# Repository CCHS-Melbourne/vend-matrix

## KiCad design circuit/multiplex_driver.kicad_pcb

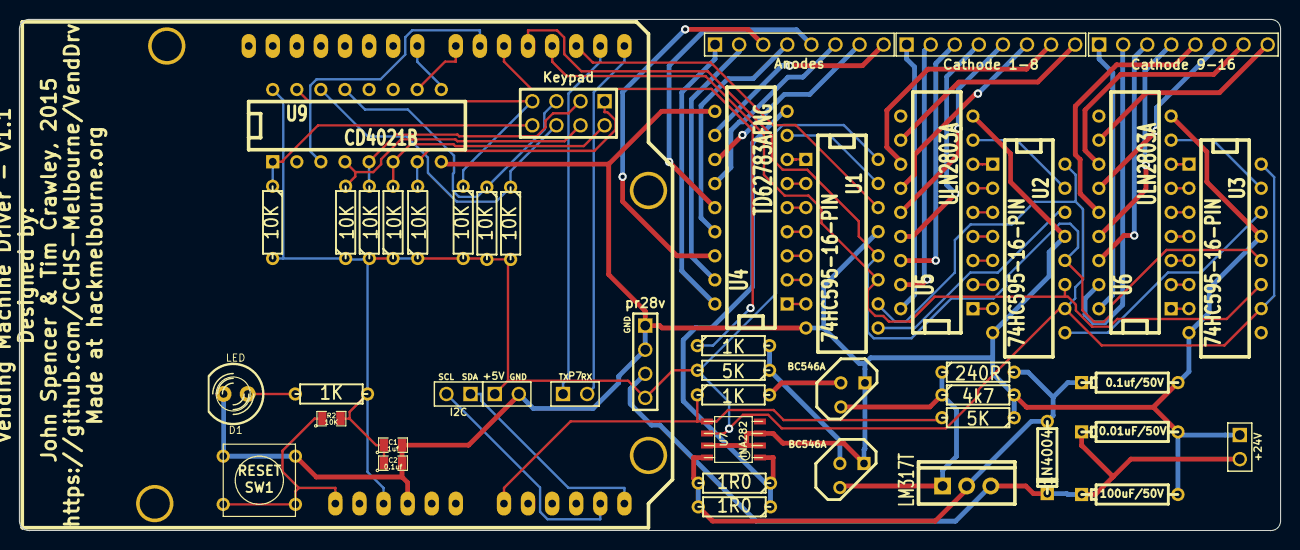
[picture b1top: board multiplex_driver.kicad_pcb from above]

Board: 2 copper layers, 133.0 x 53.9 mm, 47 parts (0 on the bottom side), 80 nets.

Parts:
C1: 1uf; SM0805
C2: 0.1uf; SM0805
C3: 100uF/50V; CP4
C4: 0.01uF/50V; CP4
C5: 0.1uf/50V; CP4
D1: LED; LED-5MM
D2: 1N4004; D3
P1: Keypad; pin_array_4x2
P2: I2C; PIN_ARRAY_2X1
P3: +5V; PIN_ARRAY_2X1
P4: Anodes; pin_array_8x1
P5: Cathode 1-8; pin_array_8x1
P6: Cathode 9-16; pin_array_8x1
P7: Serial; PIN_ARRAY_2X1
P8: +24V; PIN_ARRAY_2X1
P9: pr28v; PIN_ARRAY_4x1
Q1, Q2: BC546A; TO92
R1, R3, R6: 1K; R3
R2: 10K; SM0805
R4, R8: 5K; R3
R5: 4k7; R3
R7: 240R; R3
R9, R10: 1R0; R3
R11, R12, R13, R14, R15, R16, R17, R18: 10K; R3
SHIELD1: ARDUINO_SHIELD
SW1: RESET; SW_PUSH_SMALL
U1, U2, U3: 74HC595-16-PIN; DIP-16__300
U4: TD62783AFNG; DIP-18__300
U5, U6: ULN2803A; DIP-18__300
U7: INA282; so-8
U8: LM317T
U9: CD4021B; DIP-16__300

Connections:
+5V: C1.1, C2.1, P3.1, P9.4, R1.1, R2.2, R8.2, R11.1, R12.1, R13.1, R14.2, R15.2, R16.2, R17.2, R18.1, SHIELD1.5V, U1.10, U1.16, U2.10, U2.16, U3.10, U3.16, U7.6, U9.16
+24V: C3.1, C4.1, D2.2, P8.2, P9.3, U8.3
GND: C1.2, C2.2, C3.2, C4.2, C5.2, D1.2, P3.2, P8.1, P9.1, P9.2, Q1.1, Q2.1, R4.1, R5.2, SHIELD1.GND1, SW1.2, U1.8, U1.13, U2.8, U2.13, U3.8, U3.13, U4.10, U5.9, U6.9, U7.2, U7.3, U7.7, U9.8
K-RCLK: SHIELD1.8, U9.9
K-SER: SHIELD1.6, U9.3
K-SRCLK: SHIELD1.7, U9.10
M-ON/OFF: R3.1, SHIELD1.5
M-RCLK: SHIELD1.4, U1.12, U2.12, U3.12
M-SENSE: R4.2, R6.1, SHIELD1.AD0, U7.5
M-SER: SHIELD1.2, U1.14
M-SRCLK: SHIELD1.3, U1.11, U2.11, U3.11
MOTOR+: R9.1, R10.1, U4.9, U7.1
unnamed: U3.2, U6.6
unnamed: U3.7, U6.1
unnamed: U3.6, U6.2
unnamed: U3.5, U6.3
unnamed: U3.4, U6.4
unnamed: U3.3, U6.5
unnamed: U2.5, U5.3
unnamed: U2.4, U5.4
unnamed: U2.3, U5.5
unnamed: U3.15, U6.8
unnamed: U3.1, U6.7
unnamed: P2.1, SHIELD1.AD5
unnamed: P2.2, SHIELD1.AD4
unnamed: P5.7, U5.12
unnamed: P5.8, U5.11
unnamed: P6.1, U6.18
unnamed: P6.2, U6.17
unnamed: P6.3, U6.16
unnamed: P6.4, U6.15
unnamed: P6.5, U6.14
unnamed: P6.6, U6.13
unnamed: P6.7, U6.12
unnamed: P6.8, U6.11
unnamed: P5.6, U5.13
unnamed: U1.15, U4.8
unnamed: U1.1, U4.7
unnamed: U1.2, U4.6
unnamed: P4.4, U4.15
unnamed: P4.1, U4.18
unnamed: P4.2, U4.17
unnamed: P4.3, U4.16
unnamed: P4.5, U4.14
unnamed: P4.6, U4.13
unnamed: P4.7, U4.12
unnamed: P4.8, U4.11
unnamed: P5.1, U5.18
unnamed: P5.2, U5.17
unnamed: P5.3, U5.16
unnamed: P5.4, U5.15
unnamed: P5.5, U5.14
unnamed: U2.15, U5.8
unnamed: U2.1, U5.7
unnamed: U2.2, U5.6
unnamed: U2.7, U5.1
unnamed: U2.6, U5.2
unnamed: U1.5, U4.3
unnamed: U1.7, U4.1
unnamed: U1.6, U4.2
unnamed: U1.4, U4.4
unnamed: U1.3, U4.5
unnamed: P1.1, R11.2, U9.7
unnamed: P7.1, SHIELD1.1
unnamed: P7.2, SHIELD1.0
unnamed: P1.8, R14.1, U9.1
unnamed: P1.7, R15.1, U9.15
unnamed: P1.5, R17.1, U9.13
unnamed: P1.4, R18.2, U9.4
unnamed: P1.3, R13.2, U9.5
unnamed: P1.2, R12.2, U9.6
unnamed: P1.6, R16.1, U9.14
unnamed: D1.1, R1.2
unnamed: Q2.2, R6.2
unnamed: U2.9, U3.14
unnamed: R2.1, SHIELD1.RST, SW1.1
unnamed: U1.9, U2.14
unnamed: Q1.2, R3.2, R8.1
unnamed: C5.1, D2.1, R7.2, R9.2, R10.2, U7.8, U8.2
unnamed: Q1.3, Q2.3, R5.1, R7.1, U8.1

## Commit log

2015-01-23 :circus_tent: Added .gitattributes & .gitignore files
2015-01-23 first version
    Bit of a mix of full arduino and attiny
2015-01-24 Added input for keypad
    the uno model includes the ability to connect to a keypad.
2015-01-25 Added pins for pr28v
2015-01-29 I forget, stuff!
2015-01-29 Trying to get it to ignore gerbers
2015-01-29 Yep, Derp
2015-01-29 Ignore Dropbox
2015-01-29 Updated graphics
2015-03-15 Updated for better 24v section.
2015-03-25 Updated board
2015-03-25 Working Code!
    Working lcd, spinning motor.
2015-07-28 New front panel for keypad.
2015-07-28 Motor detection routine
    Courtesy of Tim. don't blame me for these ones.
2015-07-29 Tim's final changes
